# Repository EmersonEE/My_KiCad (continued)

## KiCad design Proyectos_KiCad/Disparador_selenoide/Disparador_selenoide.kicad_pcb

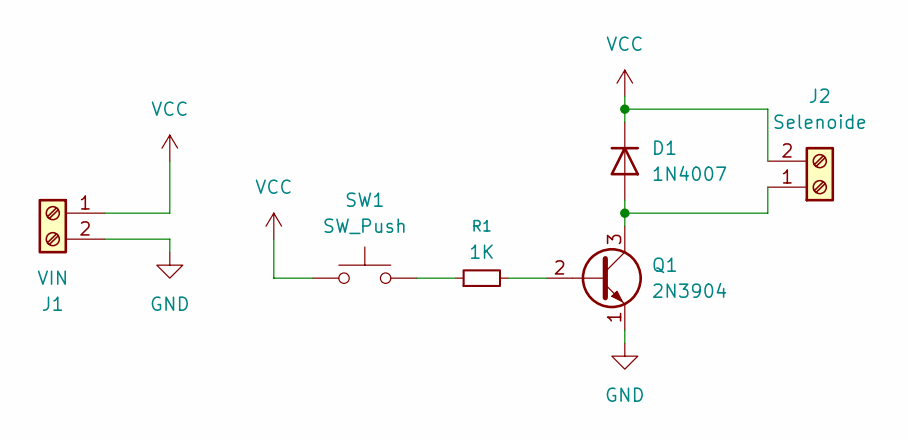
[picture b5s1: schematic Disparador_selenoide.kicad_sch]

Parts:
D1: 1N4007; D_DO-41_SOD81_P10.16mm_Horizontal
J1: VIN; TerminalBlock_Phoenix_MKDS-1,5-2-5.08_1x02_P5.08mm_Horizont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
J2: Selenoide; TerminalBlock_Phoenix_MKDS-1,5-2-5.08_1x02_P5.08mm_Horizont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
Q1: 2N3904; TO-92L_Inline_Wide
R1: 1K; R_Axial_DIN0207_L6.3mm_D2.5mm_P10.16mm_Horizontal
SW1: SW_Push; TerminalBlock_Phoenix_MKDS-1,5-2-5.08_1x02_P5.08mm_Horizont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

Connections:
GND: J1.2, Q1.1 (E)
unnamed: D1.2 (A), J2.1, Q1.3 (C)
unnamed: Q1.2 (B), R1.2
unnamed: R1.1, SW1.2
VCC: D1.1 (K), J1.1, J2.2, SW1.1

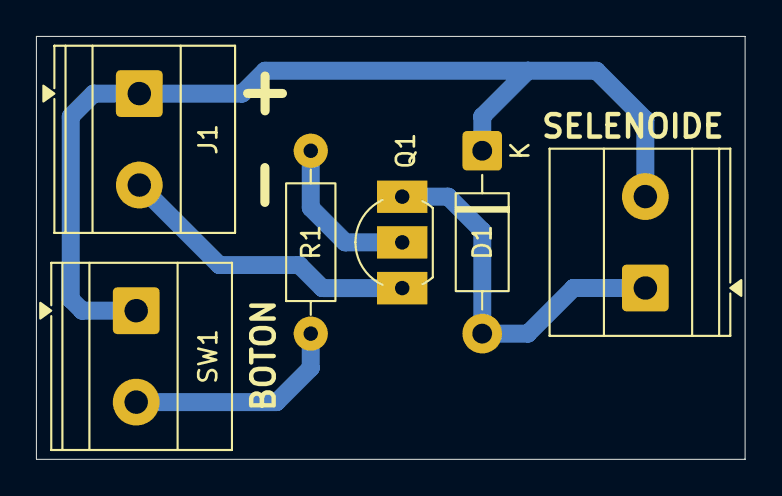
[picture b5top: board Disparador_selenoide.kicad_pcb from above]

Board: 2 copper layers, 39.4 x 23.5 mm, 6 parts (0 on the bottom side), 5 nets.

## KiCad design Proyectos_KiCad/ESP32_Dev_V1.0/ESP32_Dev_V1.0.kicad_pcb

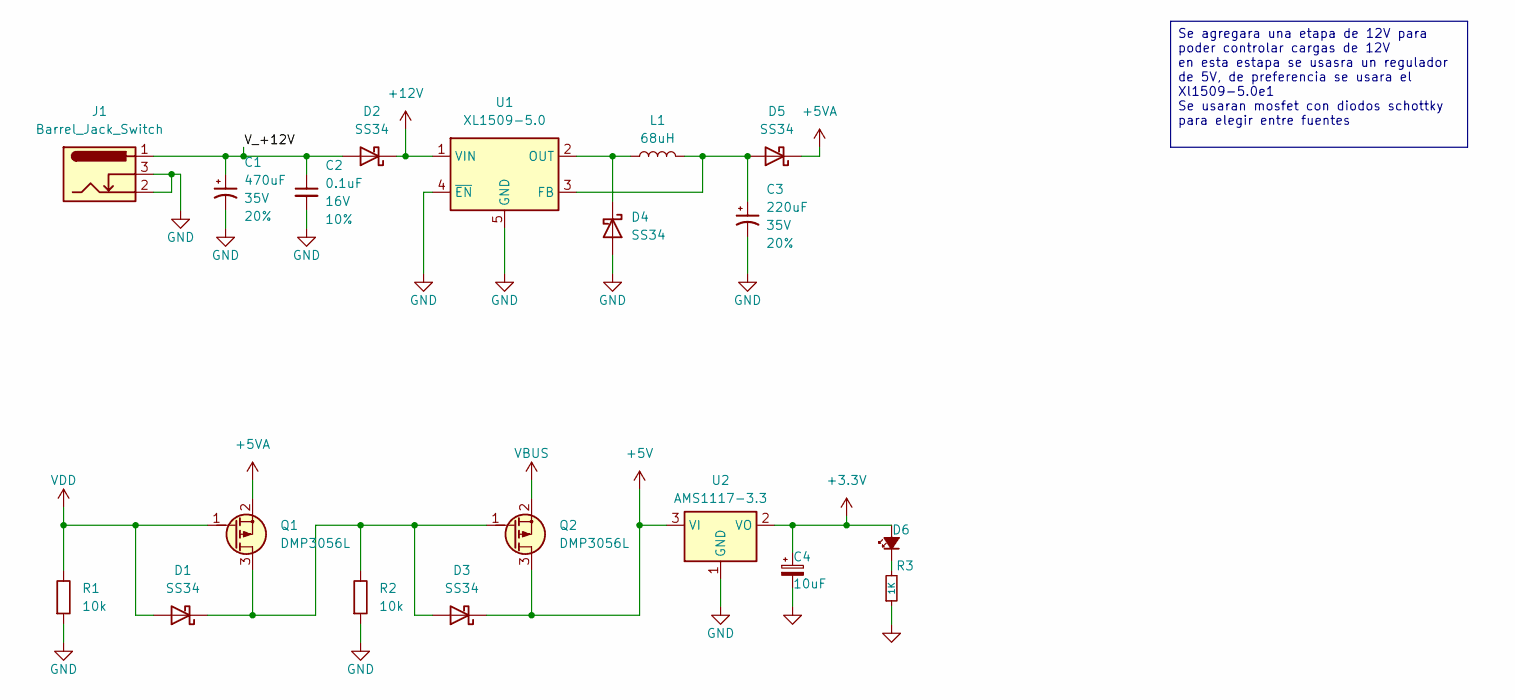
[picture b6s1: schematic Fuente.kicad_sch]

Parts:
C1: 470uF; Electrolytic_10.3x10.3mm; Voltage 35V; Tolerance 20%
C2: 0.1uF; C_0805_2012Metric; Voltage 16V; Tolerance 10%
C3: 220uF; Electrolytic_10.3x10.3mm; Voltage 35V; Tolerance 20%
C4: 10uF; CP_Elec_5x5.3; PartNo 865080642006
D1, D2, D3, D4, D5: SS34; D_SMA
D6: LED; LED_0805_2012Metric; PartNo 150060RS75000
J1: Barrel_Jack_Switch; BarrelJack_GCT_DCJ200-10-A_Horizontal
L1: 68uH; L_AVX_LMLP07A7
Q1, Q2: DMP3056L; SOT-23
R1, R2: 10k; R_0805_2012Metric
R3: 1K; R_0805_2012Metric; PartNo RC0805FR-071KL
U1: XL1509-5.0; SOIC-8_3.9x4.9mm_P1.27mm
U2: AMS1117-3.3; SOT-223-3_TabPin2

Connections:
+3.3V: C4.1, D6.2 (A), U2.2 (VO); also elsewhere on the board
+5V: D3.1 (K), Q2.3 (D), U2.3 (VI); also elsewhere on the board
+5VA: D5.1 (K), Q1.2 (S)
+12V: D2.1 (K), U1.1 (VIN); also elsewhere on the board
/Fuente/V_+12V: C1.1, C2.1, D2.2 (A), J1.1
GND: C1.2, C2.2, C3.2, C4.2, D4.2 (A), J1.2, J1.3, R1.1, R2.1, R3.1, U1.4 (~EN), U1.5 (GND), U1.6 (GND), U1.7 (GND), U1.8 (GND), U2.1 (GND); also elsewhere on the board
unnamed: D1.1 (K), D3.2 (A), Q1.3 (D), Q2.1 (G), R2.2
unnamed: D4.1 (K), L1.1, U1.2 (OUT)
unnamed: C3.1, D5.2 (A), L1.2, U1.3 (FB)
unnamed: D6.1 (K), R3.2
VBUS: Q2.2 (S); also elsewhere on the board
VDD: D1.2 (A), Q1.1 (G), R1.2; also elsewhere on the board

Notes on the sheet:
Se agregara una etapa de 12V para poder controlar cargas de 12V en esta estapa se usasra un regulador de 5V, de preferencia se usara el Xl1509-5.0e1 Se usaran mosfet con diodos schottky para elegir entre fuentes

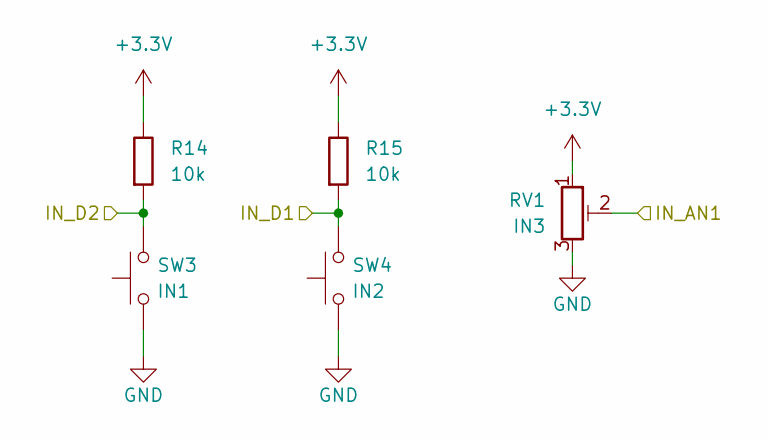
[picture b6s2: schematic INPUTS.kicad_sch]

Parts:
R14, R15: 10k; R_0805_2012Metric
RV1: IN3; Potentiometer_Bourns_3266Y_Vertical
SW3: IN1; Push_SMD_6x3.5mm; Mfg Part# 8-004 SMD Button 8x3.6mm Height=2.5mm
SW4: IN2; Push_SMD_6x3.5mm; Mfg Part# 8-004 SMD Button 8x3.6mm Height=2.5mm

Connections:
+3.3V: R14.2, R15.2, RV1.1; also elsewhere on the board
/INPUTS/IN_AN1: RV1.2; also elsewhere on the board
/INPUTS/IN_D1: R15.1, SW4.2; also elsewhere on the board
/INPUTS/IN_D2: R14.1, SW3.2; also elsewhere on the board
GND: RV1.3, SW3.1, SW4.1; also elsewhere on the board

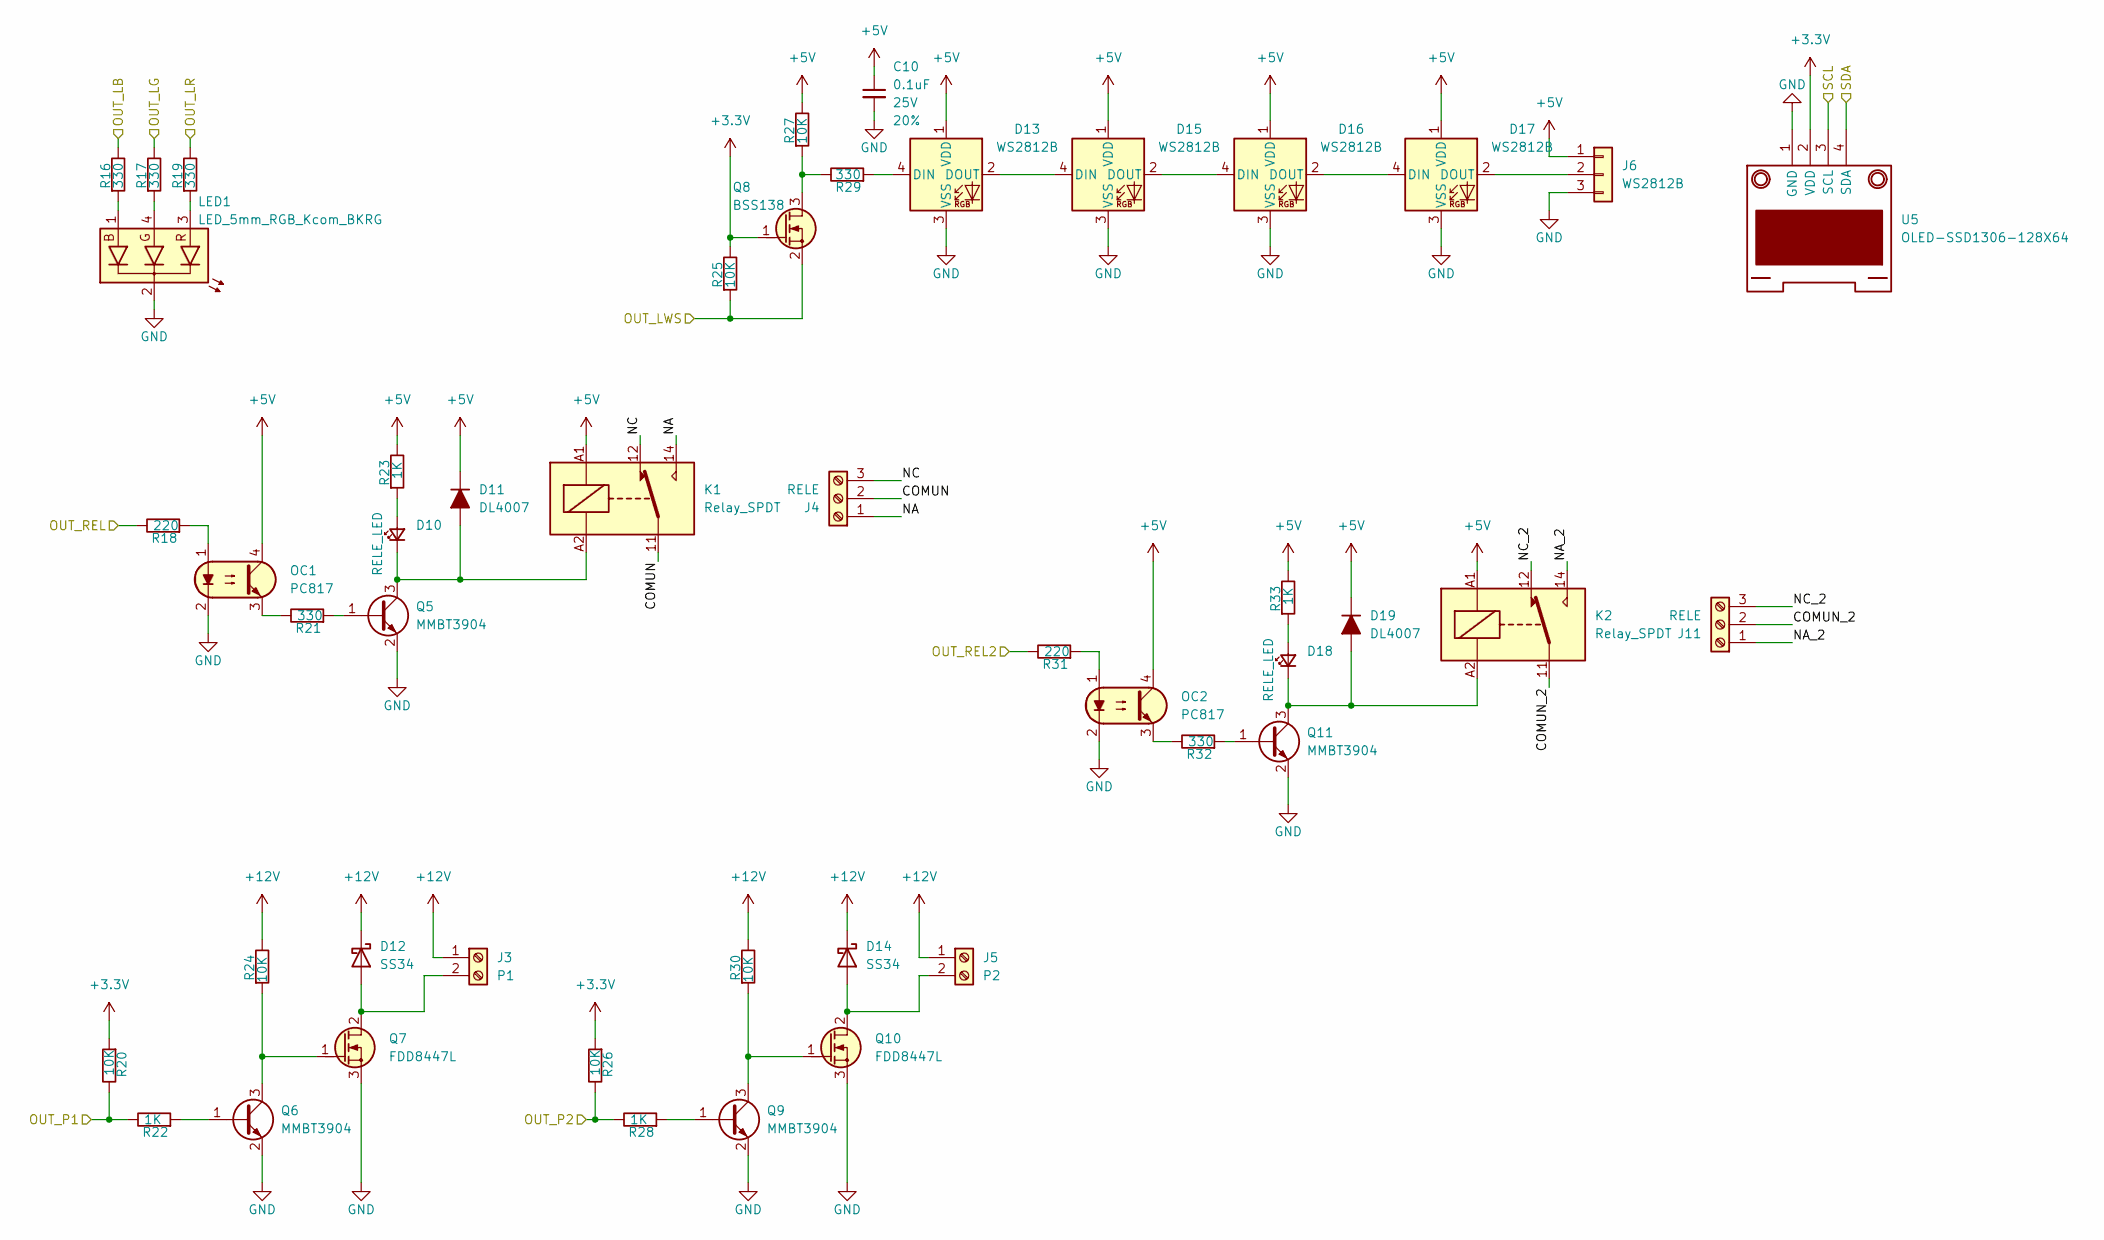
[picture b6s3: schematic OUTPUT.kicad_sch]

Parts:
C10: 0.1uF; C_0805_2012Metric; Voltage 25V; Tolerance 20%
D10, D18: RELE_LED; LED_0805_2012Metric
D11, D19: DL4007; D_SMA
D12, D14: SS34; D_SMA
D13, D15, D16, D17: WS2812B; LED_WS2812B_PLCC4_5.0x5.0mm_P3.2mm
J3: P1; TerminalBlock_Phoenix_MKDS-1,5-2-5.08_1x02_P5.08mm_Horizont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
J4, J11: RELE; TerminalBlock_Phoenix_MKDS-1,5-3-5.08_1x03_P5.08mm_Horizont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
J5: P2; TerminalBlock_Phoenix_MKDS-1,5-2-5.08_1x02_P5.08mm_Horizont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
J6: WS2812B; Molex_KK-254_AE-6410-03A_1x03_P2.54mm_Vertical
K1, K2: Relay_SPDT; Relay_SPDT_Finder_36.11
LED1: LED_5mm_RGB_Kcom_BKRG; LED_D5.0mm-4_RGB_Wide_Pins
OC1, OC2: PC817; DIP-4_W7.62mm_LongPads
Q5, Q6, Q9, Q11: MMBT3904; SOT-23
Q7, Q10: FDD8447L; TO-252-2
Q8: BSS138; SOT-23
R16, R17, R19, R21, R29, R32: 330; R_0805_2012Metric
R18, R31: 220; R_0805_2012Metric
R20, R24, R25, R26, R27, R30: 10K; R_0805_2012Metric
R22, R23, R28, R33: 1K; R_0805_2012Metric
U5: OLED-SSD1306-128X64; PinSocket_1x04_P2.54mm_Vertical

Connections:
+3.3V: Q8.1 (G), R20.1, R25.2, R26.1, U5.2 (VDD); also elsewhere on the board
+5V: C10.1, D11.1 (K), D13.1 (VDD), D15.1 (VDD), D16.1 (VDD), D17.1 (VDD), D19.1 (K), J6.1, K1.A1, K2.A1, OC1.4, OC2.4, R23.2, R27.2, R33.2; also elsewhere on the board
+12V: D12.1 (K), D14.1 (K), J3.1, J5.1, R24.2, R30.2; also elsewhere on the board
/Microcontroller/OUT_LB: R16.2; also elsewhere on the board
/Microcontroller/OUT_LG: R17.2; also elsewhere on the board
/Microcontroller/OUT_LR: R19.2; also elsewhere on the board
/Microcontroller/OUT_LWS: Q8.2 (S), R25.1; also elsewhere on the board
/Microcontroller/OUT_P1: R20.2, R22.2; also elsewhere on the board
/Microcontroller/OUT_P2: R26.2, R28.2; also elsewhere on the board
/Microcontroller/OUT_REL: R18.2; also elsewhere on the board
/Microcontroller/OUT_REL2: R31.2; also elsewhere on the board
/Microcontroller/SCL: U5.3 (SCL); also elsewhere on the board
/Microcontroller/SDA: U5.4 (SDA); also elsewhere on the board
/OUTPUT/COMUN: J4.2, K1.11
/OUTPUT/COMUN_2: J11.2, K2.11
/OUTPUT/NA: J4.1, K1.14
/OUTPUT/NA_2: J11.1, K2.14
/OUTPUT/NC: J4.3, K1.12
/OUTPUT/NC_2: J11.3, K2.12
GND: C10.2, D13.3 (VSS), D15.3 (VSS), D16.3 (VSS), D17.3 (VSS), J6.3, LED1.2 (A), OC1.2, OC2.2, Q5.2 (E), Q6.2 (E), Q7.3 (S), Q9.2 (E), Q10.3 (S), Q11.2 (E), U5.1 (GND); also elsewhere on the board
unnamed: D10.2 (A), R23.1
unnamed: D10.1 (K), D11.2 (A), K1.A2, Q5.3 (C)
unnamed: D12.2 (A), J3.2, Q7.2 (D)
unnamed: D13.4 (DIN), R29.1
unnamed: D13.2 (DOUT), D15.4 (DIN)
unnamed: D14.2 (A), J5.2, Q10.2 (D)
unnamed: D15.2 (DOUT), D16.4 (DIN)
unnamed: D16.2 (DOUT), D17.4 (DIN)
unnamed: D17.2 (DOUT), J6.2
unnamed: D18.2 (A), R33.1
unnamed: D18.1 (K), D19.2 (A), K2.A2, Q11.3 (C)
unnamed: LED1.1 (B), R16.1
unnamed: LED1.4 (G), R17.1
unnamed: LED1.3 (R), R19.1
unnamed: OC1.1, R18.1
unnamed: OC1.3, R21.2
unnamed: OC2.1, R31.1
unnamed: OC2.3, R32.2
unnamed: Q5.1 (B), R21.1
unnamed: Q6.1 (B), R22.1
unnamed: Q6.3 (C), Q7.1 (G), R24.1
unnamed: Q8.3 (D), R27.1, R29.2
unnamed: Q9.1 (B), R28.1
unnamed: Q9.3 (C), Q10.1 (G), R30.1
unnamed: Q11.1 (B), R32.1

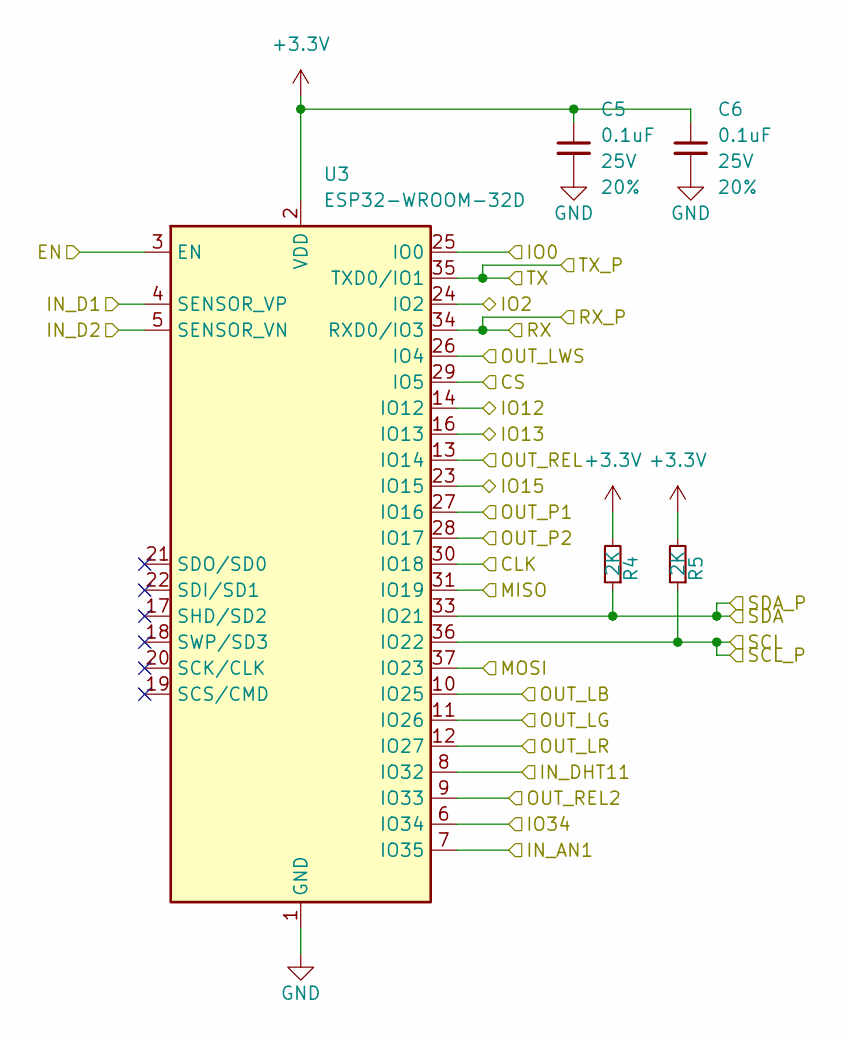
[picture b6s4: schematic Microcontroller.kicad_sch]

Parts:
C5, C6: 0.1uF; C_0805_2012Metric; Voltage 25V; Tolerance 20%
R4, R5: 2K; R_0805_2012Metric
U3: ESP32-WROOM-32D

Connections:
+3.3V: C5.1, C6.1, R4.2, R5.2, U3.2 (VDD); also elsewhere on the board
/INPUTS/IN_AN1: U3.7 (IO35); also elsewhere on the board
/INPUTS/IN_D1: U3.4 (SENSOR_VP); also elsewhere on the board
/INPUTS/IN_D2: U3.5 (SENSOR_VN); also elsewhere on the board
/Microcontroller/CLK: U3.30 (IO18); also elsewhere on the board
/Microcontroller/CS: U3.29 (IO5); also elsewhere on the board
/Microcontroller/IN_DHT11: U3.8 (IO32); also elsewhere on the board
/Microcontroller/IO2: U3.24 (IO2); also elsewhere on the board
/Microcontroller/IO12: U3.14 (IO12); also elsewhere on the board
/Microcontroller/IO13: U3.16 (IO13); also elsewhere on the board
/Microcontroller/IO15: U3.23 (IO15); also elsewhere on the board
/Microcontroller/IO34: U3.6 (IO34); also elsewhere on the board
/Microcontroller/MISO: U3.31 (IO19); also elsewhere on the board
/Microcontroller/MOSI: U3.37 (IO23); also elsewhere on the board
/Microcontroller/OUT_LB: U3.10 (IO25); also elsewhere on the board
/Microcontroller/OUT_LG: U3.11 (IO26); also elsewhere on the board
/Microcontroller/OUT_LR: U3.12 (IO27); also elsewhere on the board
/Microcontroller/OUT_LWS: U3.26 (IO4); also elsewhere on the board
/Microcontroller/OUT_P1: U3.27 (IO16); also elsewhere on the board
/Microcontroller/OUT_P2: U3.28 (IO17); also elsewhere on the board
/Microcontroller/OUT_REL: U3.13 (IO14); also elsewhere on the board
/Microcontroller/OUT_REL2: U3.9 (IO33); also elsewhere on the board
/Microcontroller/RX: U3.34 (RXD0/IO3); also elsewhere on the board
/Microcontroller/SCL: R5.1, U3.36 (IO22); also elsewhere on the board
/Microcontroller/SDA: R4.1, U3.33 (IO21); also elsewhere on the board
/Microcontroller/TX: U3.35 (TXD0/IO1); also elsewhere on the board
/USB/EN: U3.3 (EN); also elsewhere on the board
/USB/IO0: U3.25 (IO0); also elsewhere on the board
GND: C5.2, C6.2, U3.1 (GND), U3.15 (GND), U3.38 (GND), U3.39 (GND); also elsewhere on the board

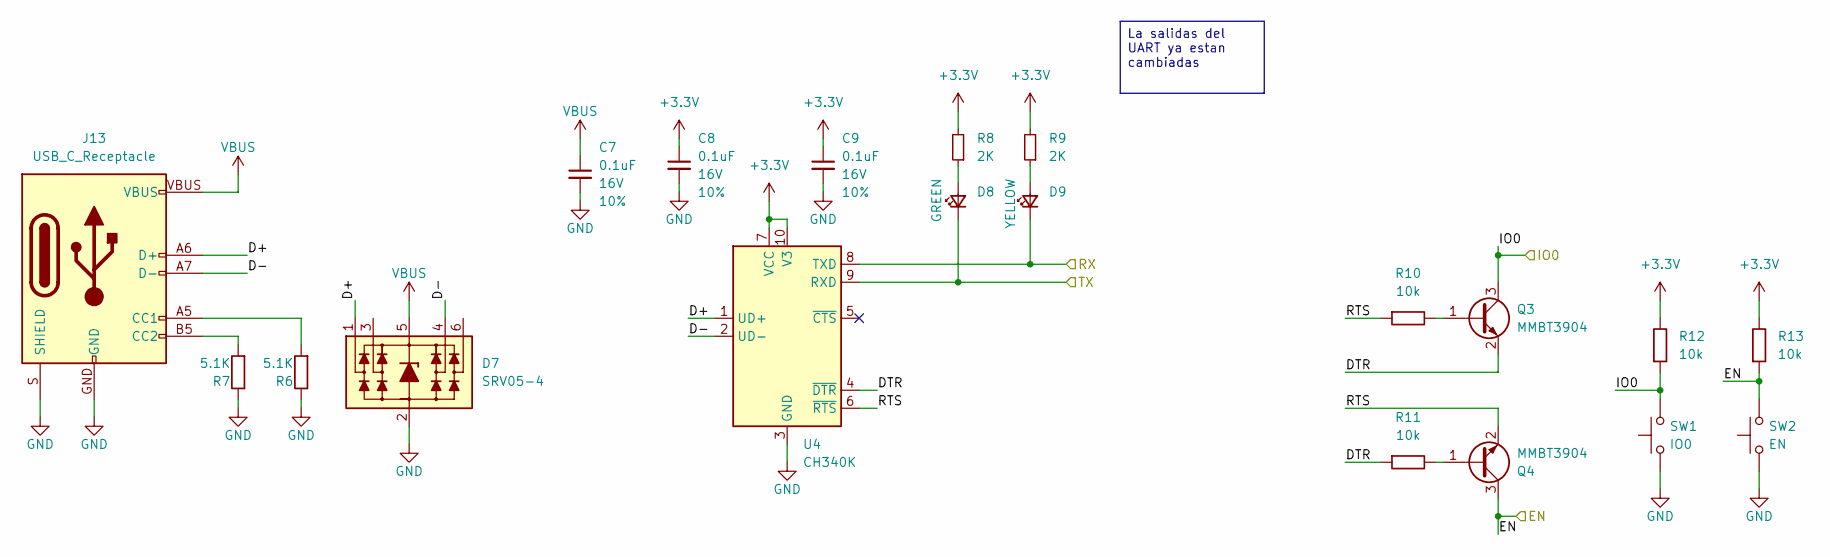
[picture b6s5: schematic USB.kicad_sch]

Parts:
C7, C8, C9: 0.1uF; C_0805_2012Metric; Voltage 16V; Tolerance 10%
D7: SRV05-4; SOT-23-6
D8: GREEN; LED_0805_2012Metric
D9: YELLOW; LED_0805_2012Metric
J13: USB_C_Receptacle; USB-C_16
Q3, Q4: MMBT3904; SOT-23
R6, R7: 5.1K; R_0805_2012Metric
R8, R9: 2K; R_0805_2012Metric
R10, R11, R12, R13: 10k; R_0805_2012Metric
SW1: IO0; Push_SMD_6x3.5mm; Mfg Part# 8-004 SMD Button 8x3.6mm Height=2.5mm
SW2: EN; Push_SMD_6x3.5mm; Mfg Part# 8-004 SMD Button 8x3.6mm Height=2.5mm
U4: CH340K; SSOP-10-1EP_3.9x4.9mm_P1mm_EP2.1x3.3mm

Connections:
+3.3V: C8.1, C9.1, R8.2, R9.2, R12.2, R13.2, U4.7 (VCC), U4.10 (V3); also elsewhere on the board
/Microcontroller/RX: D9.1 (K), U4.8 (TXD); also elsewhere on the board
/Microcontroller/TX: D8.1 (K), U4.9 (RXD); also elsewhere on the board
/USB/D+: D7.1 (L1), J13.A6 (D+), J13.B6 (D+), U4.1 (UD+)
/USB/D-: D7.4 (L3), J13.A7 (D-), J13.B7 (D-), U4.2 (UD-)
/USB/DTR: Q3.2 (E), R11.1, U4.4 (~DTR)
/USB/EN: Q4.3 (C), R13.1, SW2.2; also elsewhere on the board
/USB/IO0: Q3.3 (C), R12.1, SW1.2; also elsewhere on the board
/USB/RTS: Q4.2 (E), R10.1, U4.6 (~RTS)
GND: C7.2, C8.2, C9.2, D7.2 (VN), J13.GND, J13.S (SHIELD), R6.2, R7.2, SW1.1, SW2.1, U4.3 (GND), U4.11 (GND); also elsewhere on the board
unnamed: D8.2 (A), R8.1
unnamed: D9.2 (A), R9.1
unnamed: J13.A5 (CC1), R6.1
unnamed: J13.B5 (CC2), R7.1
unnamed: Q3.1 (B), R10.2
unnamed: Q4.1 (B), R11.2
VBUS: C7.1, D7.5 (VP), J13.VBUS; also elsewhere on the board

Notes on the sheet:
La salidas del UART ya estan cambiadas

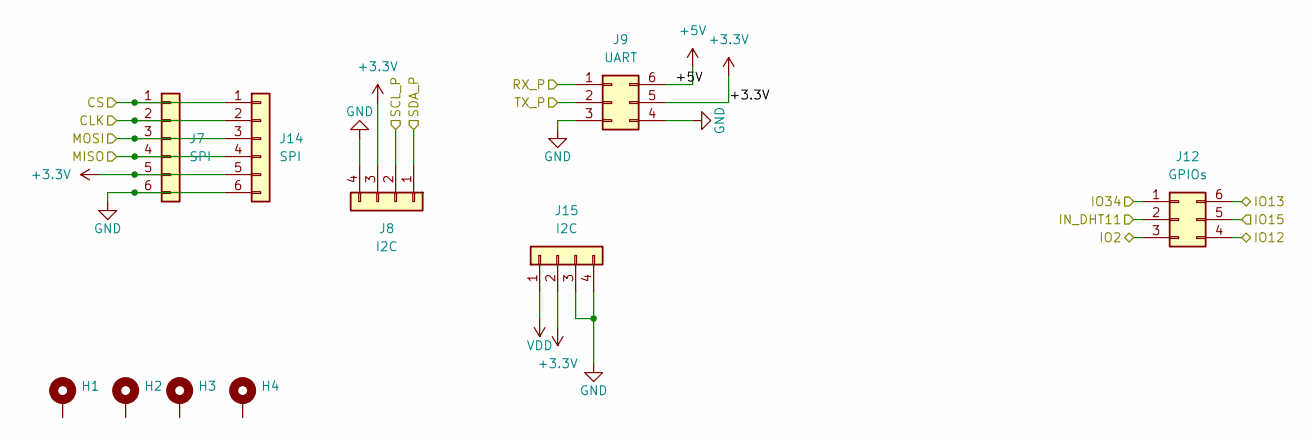
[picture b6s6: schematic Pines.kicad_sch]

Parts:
H1, H2, H3, H4: MountingHole_3.2mm_M3_Pad_Via
J7, J14: SPI; PinHeader_1x06_P2.54mm_Vertical
J8, J15: I2C; PinHeader_1x04_P2.54mm_Vertical
J9: UART; PinHeader_2x03_P2.54mm_Vertical
J12: GPIOs; PinHeader_2x03_P2.54mm_Vertical

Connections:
+3.3V: J7.5, J8.3, J9.5, J14.5, J15.2; also elsewhere on the board
+5V: J9.6; also elsewhere on the board
/Microcontroller/CLK: J7.2, J14.2; also elsewhere on the board
/Microcontroller/CS: J7.1, J14.1; also elsewhere on the board
/Microcontroller/IN_DHT11: J12.2; also elsewhere on the board
/Microcontroller/IO2: J12.3; also elsewhere on the board
/Microcontroller/IO12: J12.4; also elsewhere on the board
/Microcontroller/IO13: J12.6; also elsewhere on the board
/Microcontroller/IO15: J12.5; also elsewhere on the board
/Microcontroller/IO34: J12.1; also elsewhere on the board
/Microcontroller/MISO: J7.4, J14.4; also elsewhere on the board
/Microcontroller/MOSI: J7.3, J14.3; also elsewhere on the board
/Microcontroller/RX: J9.1; also elsewhere on the board
/Microcontroller/SCL: J8.2; also elsewhere on the board
/Microcontroller/SDA: J8.1; also elsewhere on the board
/Microcontroller/TX: J9.2; also elsewhere on the board
GND: J7.6, J8.4, J9.3, J9.4, J14.6, J15.3, J15.4; also elsewhere on the board
VDD: J15.1; also elsewhere on the board

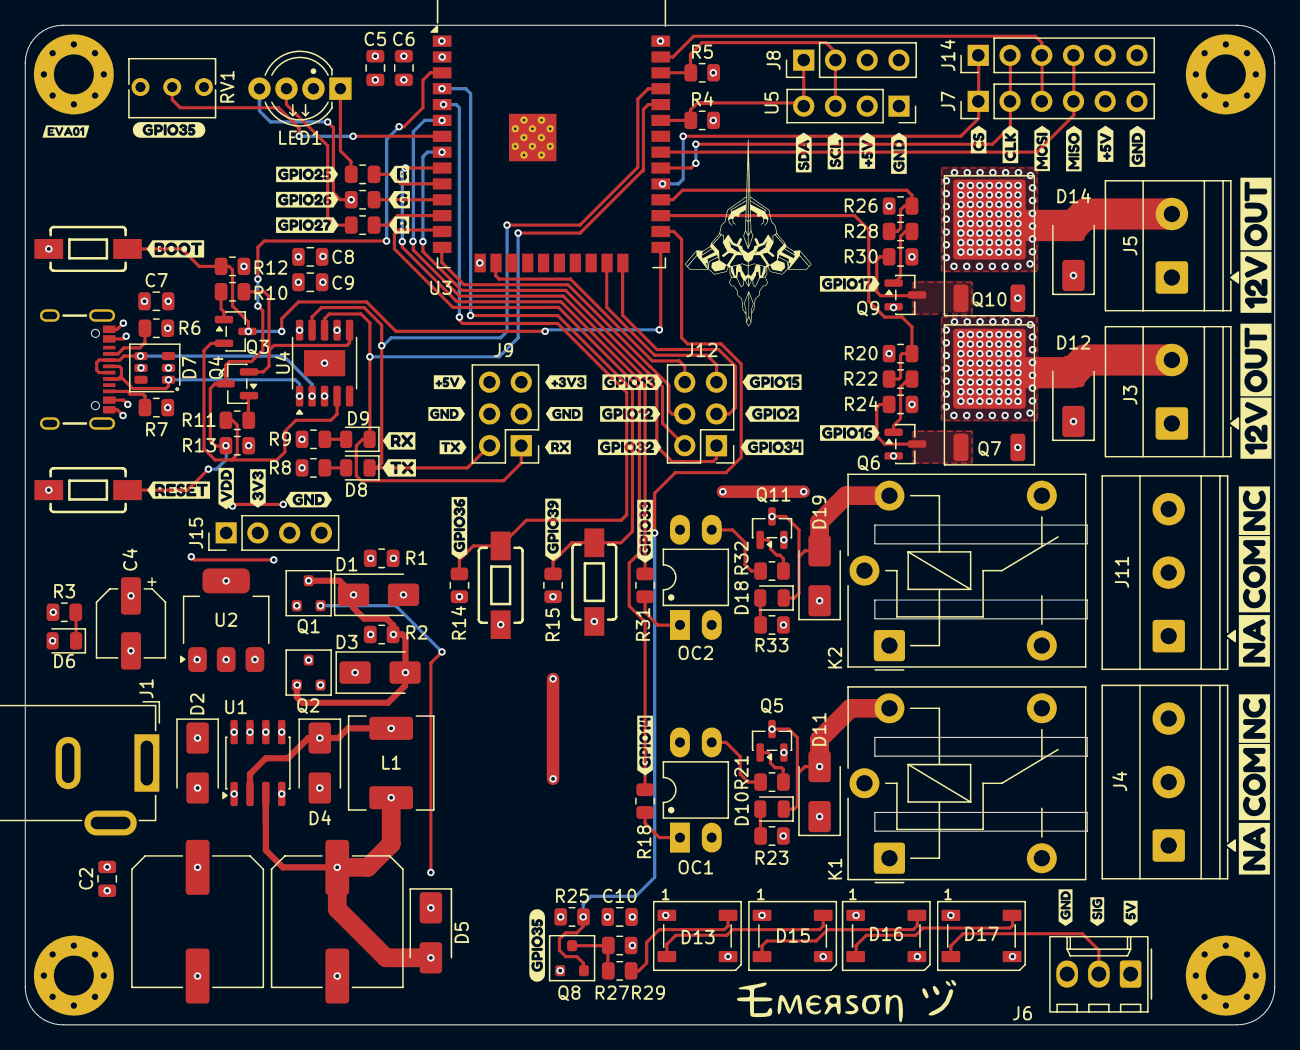
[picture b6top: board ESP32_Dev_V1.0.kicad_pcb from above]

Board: 4 copper layers, 100.0 x 80.0 mm, 163 parts (0 on the bottom side), 80 nets.

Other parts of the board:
kibuzzard-6A84A55A: G***; kibuzzard-6A84A55A
kibuzzard-6A84A561: G***; kibuzzard-6A84A561
kibuzzard-6A727BCE: G***; kibuzzard-6A727BCE
kibuzzard-6A727C1E: G***; kibuzzard-6A727C1E
kibuzzard-6A727C6D: G***; kibuzzard-6A727C6D
kibuzzard-6A727C11: G***; kibuzzard-6A727C11
kibuzzard-6A727C18: G***; kibuzzard-6A727C18
kibuzzard-6A727C24, kibuzzard-6A727C24#2: G***; kibuzzard-6A727C24
kibuzzard-6A727C29, kibuzzard-6A727C29#2: G***; kibuzzard-6A727C29
kibuzzard-6A727C74: G***; kibuzzard-6A727C74
kibuzzard-6A727DDB: G***; kibuzzard-6A727DDB
kibuzzard-6A727DF1: G***; kibuzzard-6A727DF1
kibuzzard-6A727ECC, kibuzzard-6A727ECC#2: G***; kibuzzard-6A727ECC
kibuzzard-6A727ED5, kibuzzard-6A727ED5#2: G***; kibuzzard-6A727ED5
kibuzzard-6A849D4A: G***; kibuzzard-6A849D4A
kibuzzard-6A849D5B: G***; kibuzzard-6A849D5B
kibuzzard-6A849D8D: G***; kibuzzard-6A849D8D
kibuzzard-6A849D44: G***; kibuzzard-6A849D44
kibuzzard-6A849D67: G***; kibuzzard-6A849D67
kibuzzard-6A849D93: G***; kibuzzard-6A849D93
kibuzzard-6A7277D2: G***; kibuzzard-6A7277D2
kibuzzard-6A7277EF: G***; kibuzzard-6A7277EF
kibuzzard-6A7277F6: G***; kibuzzard-6A7277F6
kibuzzard-6A7278E0: G***; kibuzzard-6A7278E0
kibuzzard-6A7278F5: G***; kibuzzard-6A7278F5
kibuzzard-6A7279A2, kibuzzard-6A7279A2#2: G***; kibuzzard-6A7279A2
kibuzzard-6A7280AD: G***; kibuzzard-6A7280AD
kibuzzard-6A7281CE: G***; kibuzzard-6A7281CE
kibuzzard-6A7281DF: G***; kibuzzard-6A7281DF
kibuzzard-6A7281E6: G***; kibuzzard-6A7281E6
kibuzzard-6A7283B1: G***; kibuzzard-6A7283B1
kibuzzard-6A72633A, kibuzzard-6A72633A#2: G***; kibuzzard-6A72633A
kibuzzard-6A72791D: G***; kibuzzard-6A72791D
kibuzzard-6A72793C: G***; kibuzzard-6A72793C
kibuzzard-6A72838F: G***; kibuzzard-6A72838F
kibuzzard-6A726309, kibuzzard-6A726309#2: G***; kibuzzard-6A726309
kibuzzard-6A726341, kibuzzard-6A726341#2: G***; kibuzzard-6A726341
kibuzzard-6A727472: G***; kibuzzard-6A727472
kibuzzard-6A727479: G***; kibuzzard-6A727479
kibuzzard-6A727480: G***; kibuzzard-6A727480
kibuzzard-6A727489: G***; kibuzzard-6A727489
kibuzzard-6A727492: G***; kibuzzard-6A727492
kibuzzard-6A727498: G***; kibuzzard-6A727498
kibuzzard-6A727942: G***; kibuzzard-6A727942
kibuzzard-6A727946: G***; kibuzzard-6A727946
kibuzzard-6A728113: G***; kibuzzard-6A728113
kibuzzard-6A728159: G***; kibuzzard-6A728159
kibuzzard-6A728349: G***; kibuzzard-6A728349
kibuzzard-6A728389: G***; kibuzzard-6A728389

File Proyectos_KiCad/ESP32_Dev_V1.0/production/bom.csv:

Designator,Footprint,Quantity,Value,LCSC Part #
C1,Electrolytic_10.3x10.3mm,1,470uF,
"C10, C2, C5, C6, C7, C8, C9",0805,7,0.1uF,
C3,Electrolytic_10.3x10.3mm,1,220uF,
C4,CP_Elec_5x5.3,1,10uF,
"D1, D12, D14, D2, D3, D4, D5",D_SMA,7,SS34,
"D10, D18",0805,2,RELE_LED,
"D11, D19",D_SMA,2,DL4007,
"D13, D15, D16, D17",LED_WS2812B_PLCC4_5.0x5.0mm_P3.2mm,4,WS2812B,
D6,0805,1,LED,
D7,SOT-23-6,1,SRV05-4,
D8,0805,1,GREEN,
D9,0805,1,YELLOW,
J1,BarrelJack_GCT_DCJ200-10-A_Horizontal,1,Barrel_Jack_Switch,
"J11, J4","TerminalBlock_Phoenix_MKDS-1,5-3-5.08_1x03_P5.08mm_Horizontal",2,RELE,
J12,PinHeader_2x03_P2.54mm_Vertical,1,GPIOs,
J13,USB-C_16,1,USB_C_Receptacle,
"J14, J7",PinHeader_1x06_P2.54mm_Vertical,2,SPI,
"J15, J8",PinHeader_1x04_P2.54mm_Vertical,2,I2C,
J3,"TerminalBlock_Phoenix_MKDS-1,5-2-5.08_1x02_P5.08mm_Horizontal",1,P1,
J5,"TerminalBlock_Phoenix_MKDS-1,5-2-5.08_1x02_P5.08mm_Horizontal",1,P2,
J6,Molex_KK-254_AE-6410-03A_1x03_P2.54mm_Vertical,1,WS2812B,
J9,PinHeader_2x03_P2.54mm_Vertical,1,UART,
"K1, K2",Relay_SPDT_Finder_36.11,2,Relay_SPDT,
L1,L_AVX_LMLP07A7,1,68uH,
LED1,LED_D5.0mm-4_RGB_Wide_Pins,1,LED_5mm_RGB_Kcom_BKRG,
"OC1, OC2",DIP-4_W7.62mm_LongPads,2,PC817,
"Q1, Q2",SOT-23,2,DMP3056L,
"Q10, Q7",TO-252-2,2,FDD8447L,
"Q11, Q3, Q4, Q5, Q6, Q9",SOT-23,6,MMBT3904,
Q8,SOT-23,1,BSS138,
"R1, R10, R11, R12, R13, R14, R15, R2, R20, R24, R25, R26, R27, R30",0805,14,10k,
"R16, R17, R19, R21, R29, R32",0805,6,330,
"R18, R31",0805,2,220,
"R22, R23, R28, R3, R33",0805,5,1K,
"R4, R5, R8, R9",0805,4,2K,
"R6, R7",0805,2,5.1K,
RV1,Potentiometer_Bourns_3266Y_Vertical,1,IN3,
SW1,Push_SMD_6x3.5mm,1,IO0,
SW2,Push_SMD_6x3.5mm,1,EN,
SW3,Push_SMD_6x3.5mm,1,IN1,
SW4,Push_SMD_6x3.5mm,1,IN2,
U1,SOIC-8_3.9x4.9mm_P1.27mm,1,XL1509-5.0,
U2,SOT-223-3_TabPin2,1,AMS1117-3.3,
U3,ESP32-WROOM-32D,1,ESP32-WROOM-32D,
U4,SSOP-10-1EP_3.9x4.9mm_P1mm_EP2.1x3.3mm,1,CH340K,
U5,PinSocket_1x04_P2.54mm_Vertical,1,OLED-SSD1306-128X64,

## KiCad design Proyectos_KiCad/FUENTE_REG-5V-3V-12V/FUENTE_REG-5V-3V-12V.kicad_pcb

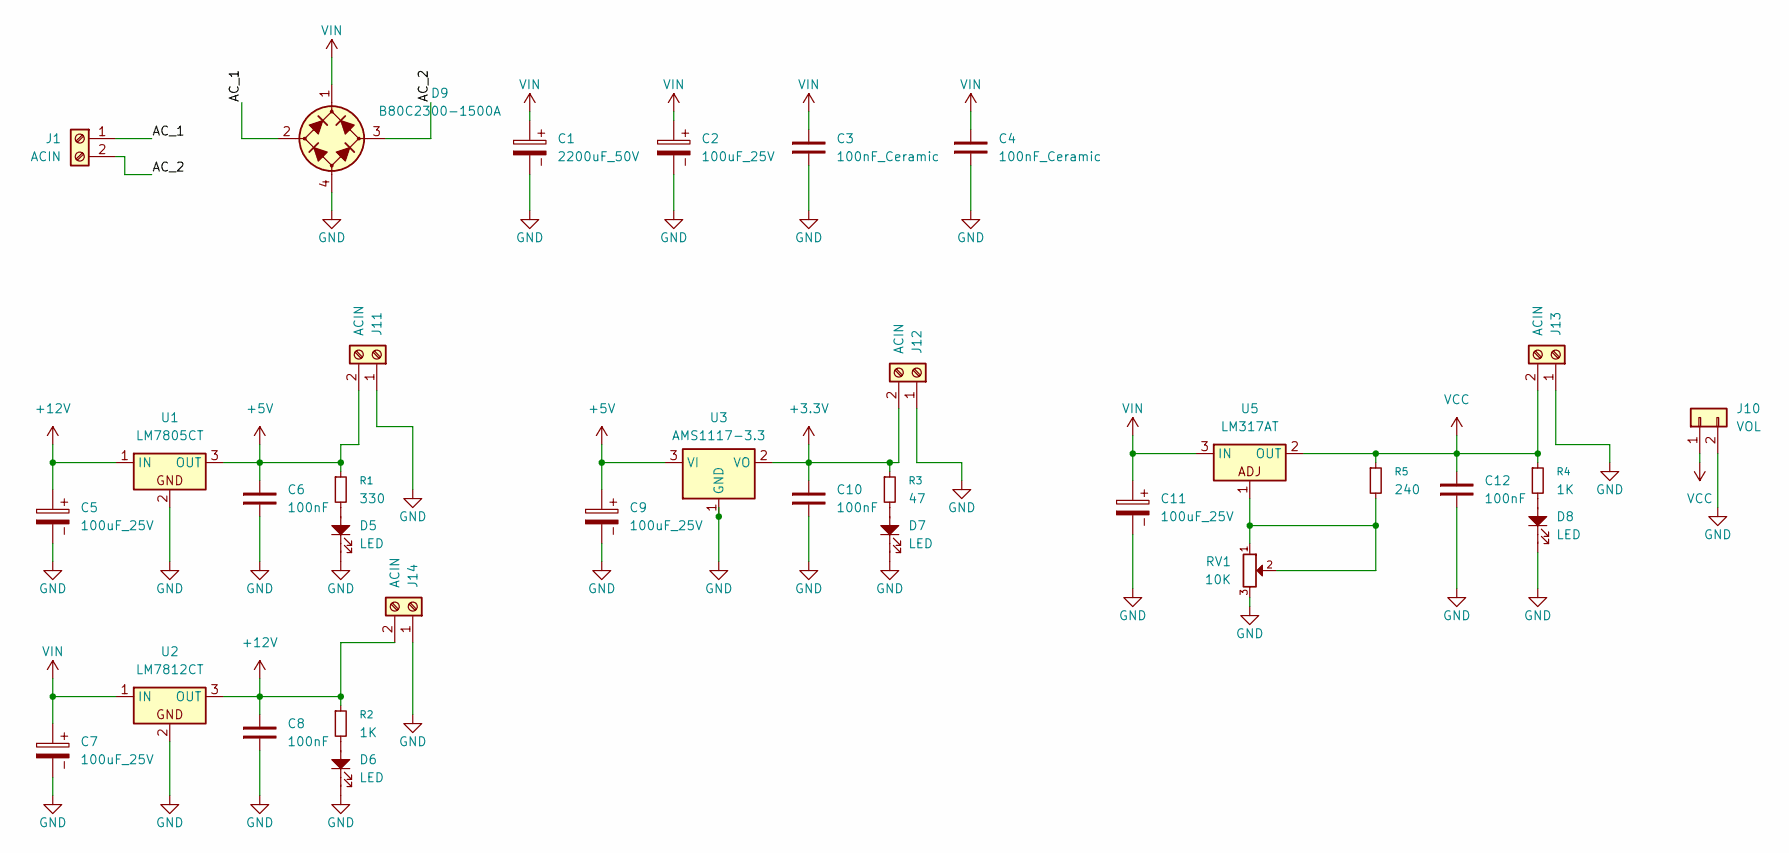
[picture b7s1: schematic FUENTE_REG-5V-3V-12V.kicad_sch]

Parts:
C1: 2200uF_50V; CP_Radial_D16.0mm_P7.50mm
C2, C5, C7, C9, C11: 100uF_25V; CP_Radial_D6.3mm_P2.50mm
C3, C4: 100nF_Ceramic; C_Disc_D5.0mm_W2.5mm_P2.50mm
C6, C8, C10, C12: 100nF; C_Disc_D5.0mm_W2.5mm_P2.50mm
D5, D6, D7, D8: LED; LED_D5.0mm
D9: B80C2300-1500A; Diode_Bridge_19.0x3.5x10.0mm_P5.0mm
J1, J11, J12, J13, J14: ACIN; TerminalBlock_MetzConnect_Type073_RT02602HBLU_1x02_P5.08mm_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
J10: VOL; Molex_KK-254_AE-6410-02A_1x02_P2.54mm_Vertical
R1: 330
R2, R4: 1K
R3: 47; 470
R5: 240; 220
RV1: 10K; Potentiometer_Alps_RK163_Single_Horizontal
U1: LM7805CT; TO-220-3_VDC
U2: LM7812CT; TO-220-3_VDC
U3: AMS1117-3.3; SOT-223-3_TabPin2
U5: LM317AT; TO-220-3_VDC

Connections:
+3.3V: C10.2, J12.2, R3.1, U3.2 (VO)
+5V: C6.2, C9.1, J11.2, R1.1, U1.3 (OUT), U3.3 (VI)
+12V: C5.1, C8.2, J14.2, R2.1, U1.1 (IN), U2.3 (OUT)
/AC_1: D9.2 (1), J1.1
/AC_2: D9.3 (2), J1.2
GND: C1.2, C2.2, C3.1, C4.1, C5.2, C6.1, C7.2, C8.1, C9.2, C10.1, C11.2, C12.1, D5.1, D6.1, D7.1, D8.1, D9.4 (-), J10.2, J11.1, J12.1, J13.1, J14.1, RV1.3, U1.2, U2.2, U3.1 (GND)
unnamed: D5.2, R1.2
unnamed: D6.2, R2.2
unnamed: D7.2, R3.2
unnamed: D8.2, R4.2
unnamed: R5.2, RV1.1, RV1.2, U5.1
VCC: C12.2, J10.1, J13.2, R4.1, R5.1, U5.2 (OUT)
VIN: C1.1, C2.1, C3.2, C4.2, C7.1, C11.1, D9.1 (+), U2.1 (IN), U5.3 (IN)

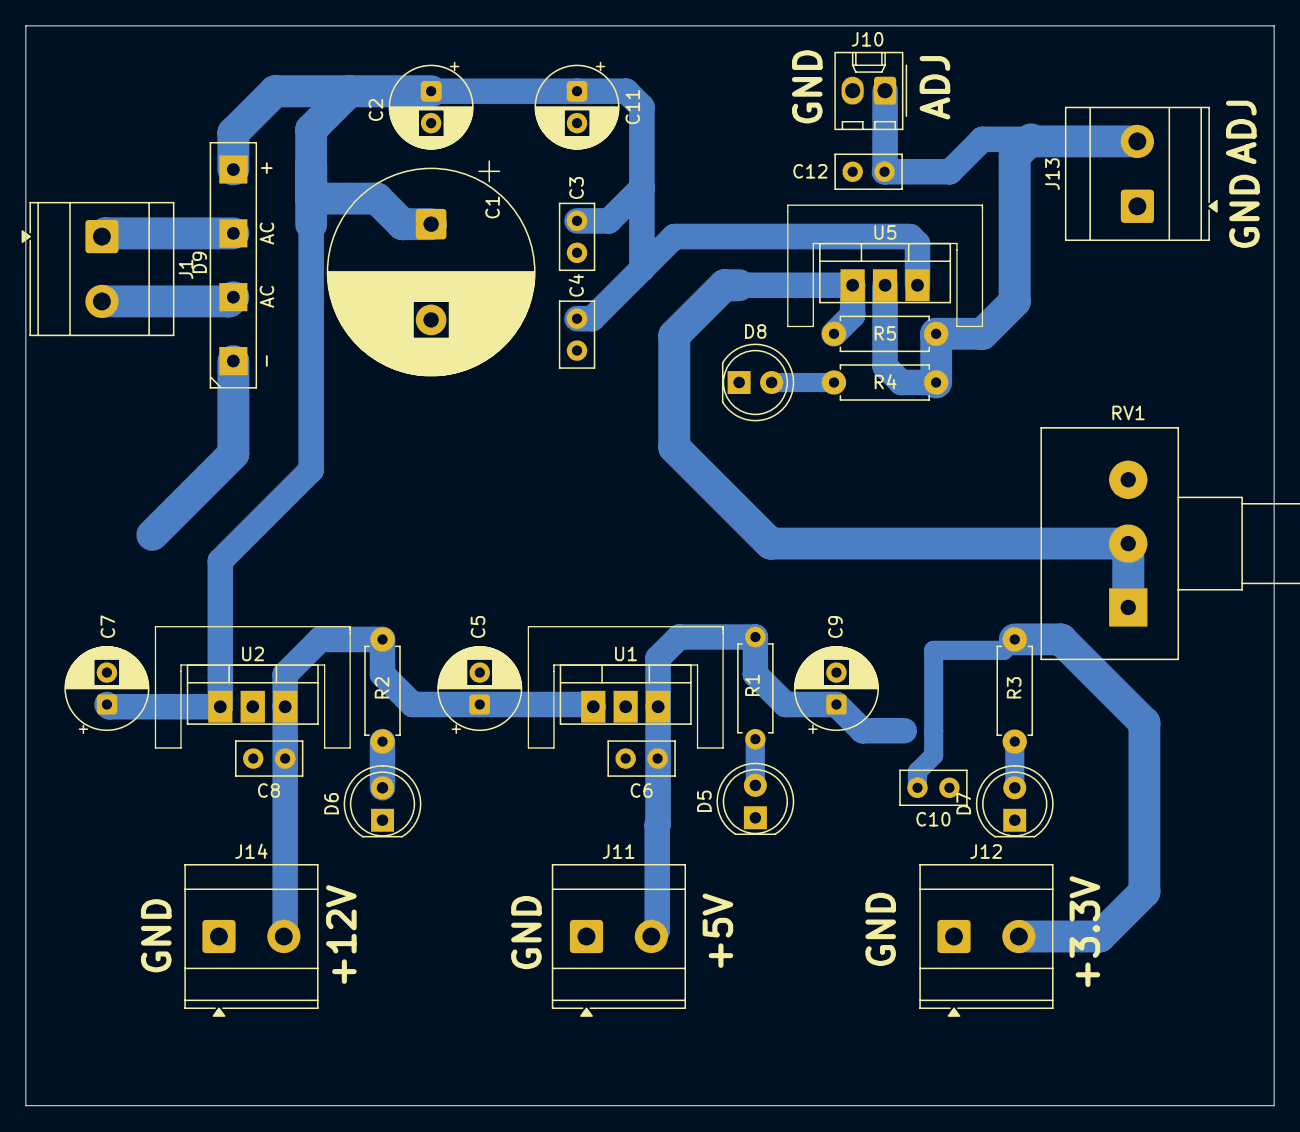
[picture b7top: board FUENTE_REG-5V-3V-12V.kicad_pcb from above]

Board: 2 copper layers, 97.8 x 84.6 mm, 33 parts (1 on the bottom side), 13 nets.
